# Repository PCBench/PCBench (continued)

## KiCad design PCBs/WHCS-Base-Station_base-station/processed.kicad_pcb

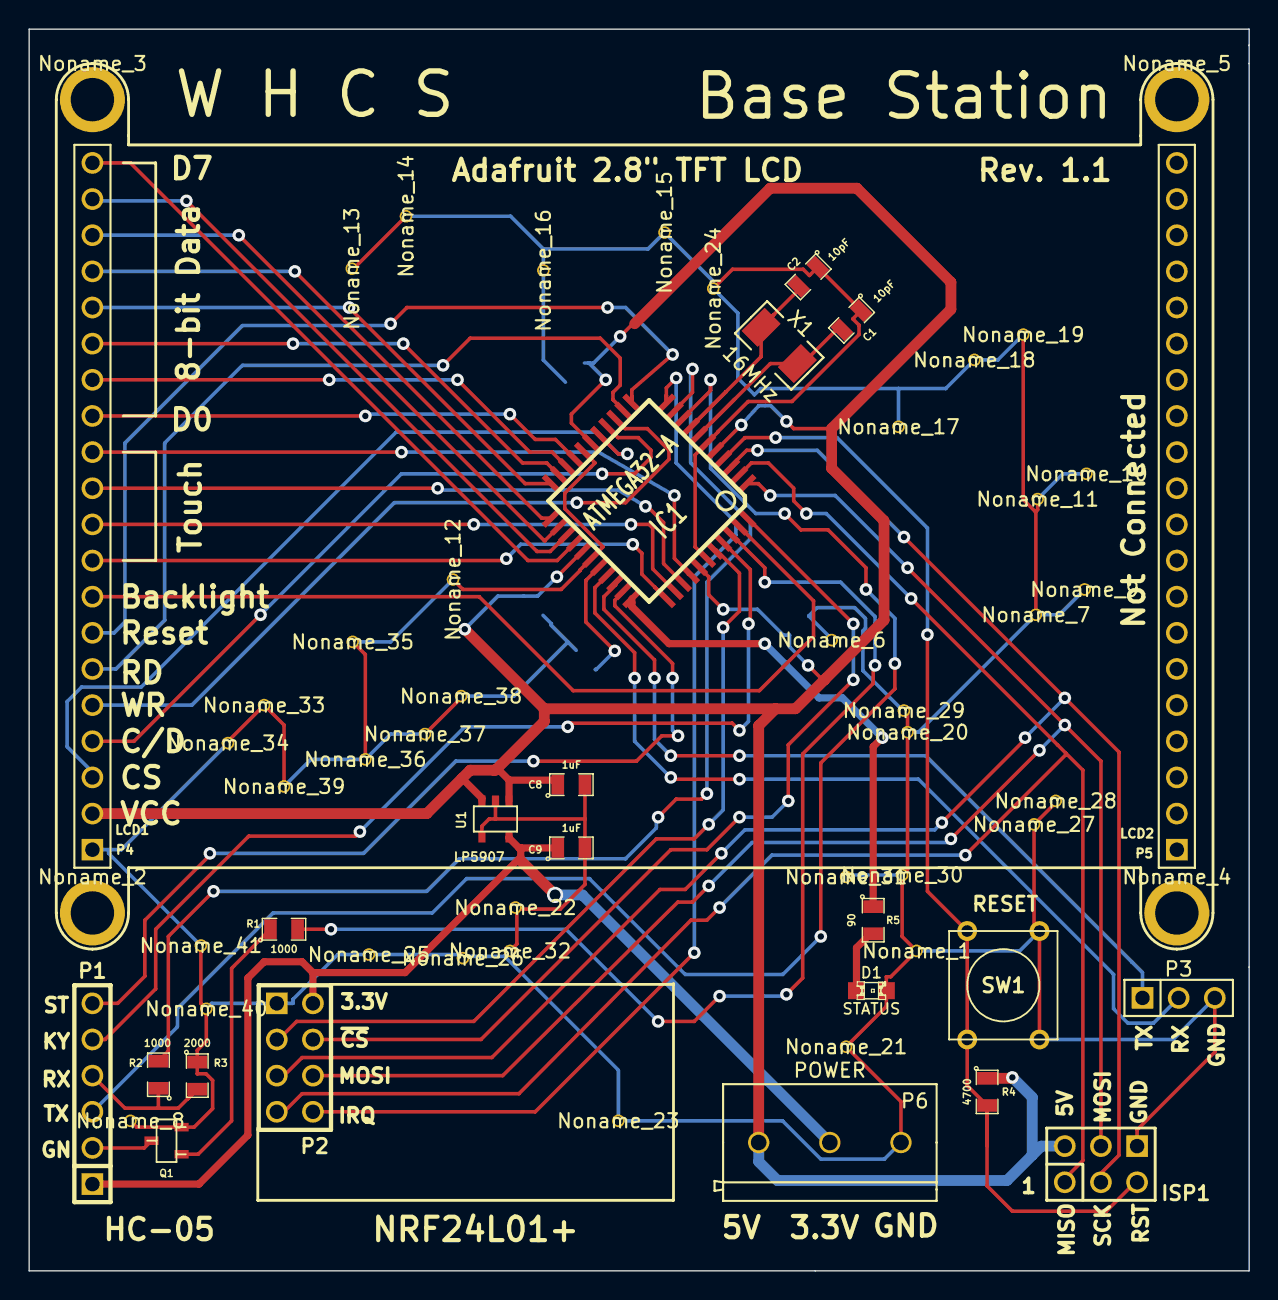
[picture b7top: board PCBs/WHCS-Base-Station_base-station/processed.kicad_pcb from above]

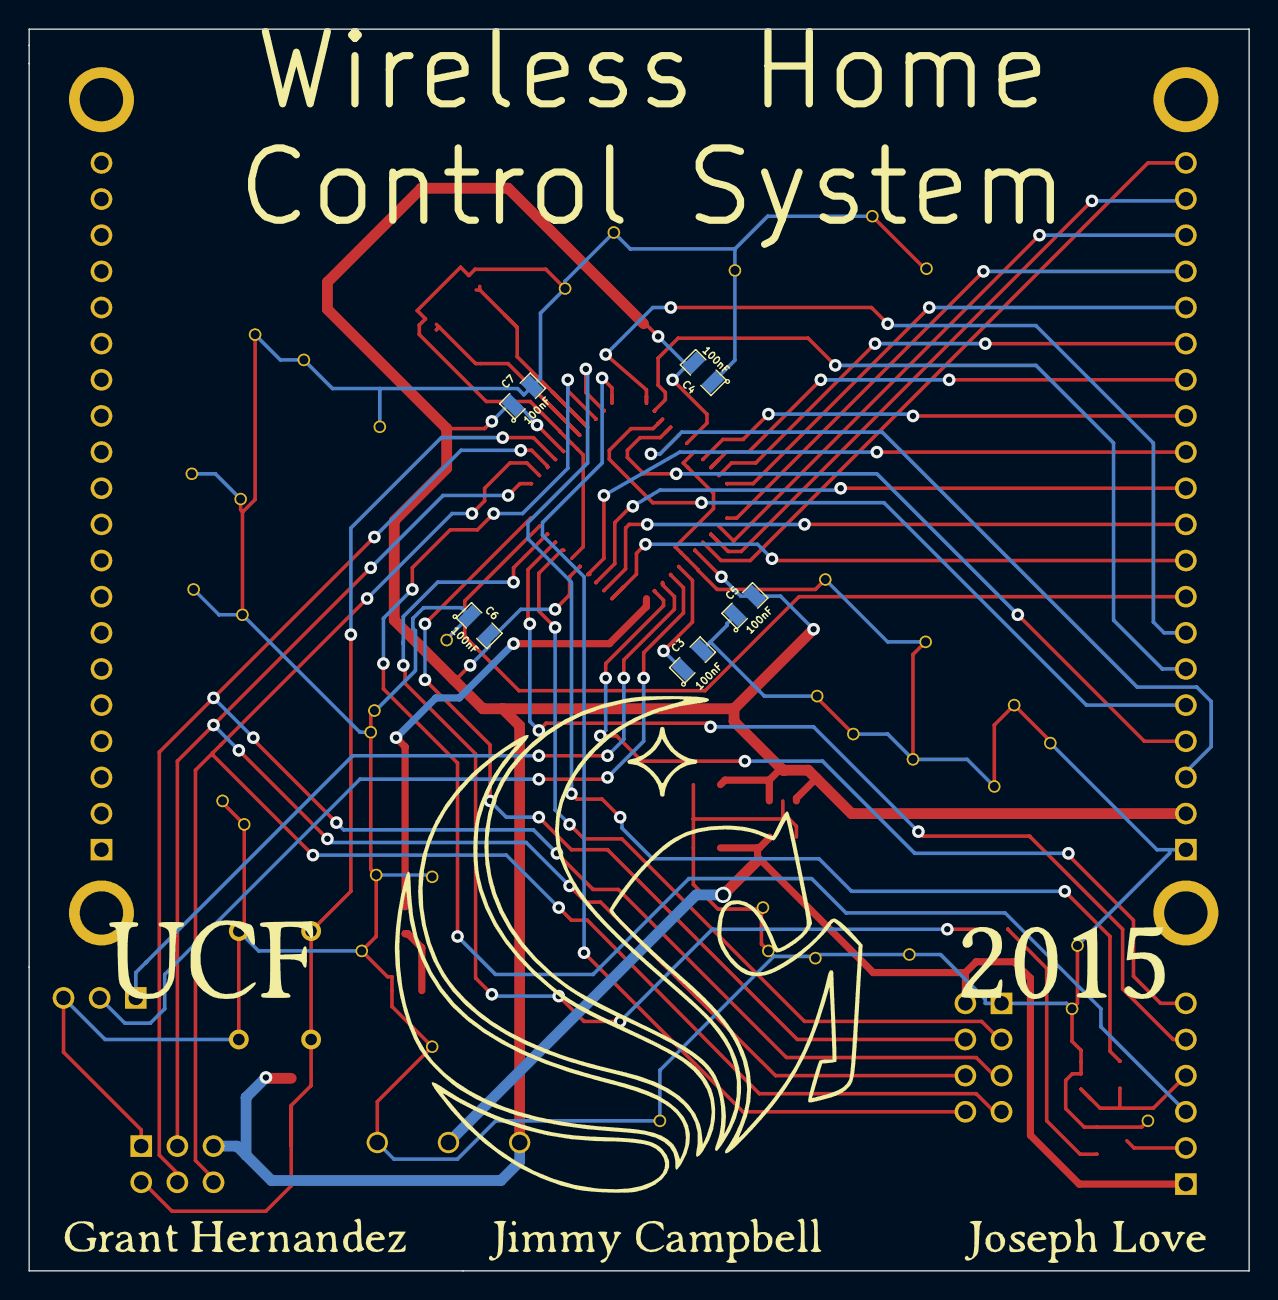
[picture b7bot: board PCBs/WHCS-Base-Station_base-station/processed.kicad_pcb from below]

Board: 2 copper layers, 85.7 x 87.2 mm, 68 parts (5 on the bottom side), 43 nets.

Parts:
C1, C2: 10pF; SM0805
C3, C4, C5, C6, C7: 100nF; SM0805
C8, C9: 1uF; SM0805
D1: STATUS; LED-0805
IC1: ATMEGA32-A; TQFP44
ISP1: ISP; pin_array_3x2
Noname_1, Noname_6, Noname_7, Noname_8, Noname_9, Noname_10, Noname_11, Noname_12, Noname_13, Noname_14, Noname_15, Noname_16, Noname_17, Noname_18, Noname_19, Noname_20, Noname_21, Noname_22, Noname_23, Noname_24, Noname_25, Noname_26, Noname_27, Noname_28, Noname_29, Noname_30, Noname_31, Noname_32, Noname_33, Noname_34, Noname_35, Noname_36, Noname_37, Noname_38, Noname_39, Noname_40, Noname_41: gnd-via
Noname_2, Noname_3, Noname_4, Noname_5: adafruit-tft-mount
P1: HC-05; PIN_ARRAY-6X1
P2: NRF24L01+; pin_array_4x2
P3: SERIAL; PIN_ARRAY_3X1
P4: LCD1; PIN_ARRAY_20X1
P5: LCD2; PIN_ARRAY_20X1
P6: POWER; terminal-282836-3
Q1: BTEN; sot23
R1, R2: 1000; SM0805
R3: 2000; SM0805
R4: 4700; SM0805
R5: 90; SM0805
SW1: RESET; SW_PUSH_SMALL
U1: LP5907; SOT23-5
X1: 16MHz; 2-SMD

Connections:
/3V3: C9.1, P1.1, P2.2, P6.2, U1.5
/BTEN: IC1.42, R1.2
/CD: IC1.15, P4.4
/CE: IC1.40, P2.3
/CSN: IC1.44, P2.4
/D0: IC1.19, P4.13
/D1: IC1.20, P4.14
/D2: IC1.21, P4.15
/D3: IC1.22, P4.16
/D4: IC1.23, P4.17
/D5: IC1.24, P4.18
/D6: IC1.25, P4.19
/D7: IC1.26, P4.20
/HC_GND: P1.2, Q1.2
/IRQ: IC1.11, P2.8
/KEY: IC1.41, P1.5
/LCS: IC1.16, P4.3
/LITE: IC1.43, P4.8
/LRST: IC1.12, P4.7
/MISO: IC1.2, ISP1.1, P2.7
/MOSI: IC1.1, ISP1.4, P2.6
/PA4: IC1.33, R5.1
/RD: IC1.13, P4.6
/RST: IC1.4, ISP1.5, R4.2, SW1.1
/RX: IC1.9, P1.3
/RX_SOFT: IC1.30, P3.2
/SCK: IC1.3, ISP1.3, P2.5
/STATUS: IC1.32, P1.6
/TX: IC1.10, R2.2
/TX_SOFT: IC1.31, P3.1
/VCC: C4.2, C5.2, C6.2, C7.1, C8.1, IC1.5, IC1.17, IC1.27, IC1.38, ISP1.2, P4.2, P6.1, R4.1, U1.1, U1.3
/WR: IC1.14, P4.5
/X+: IC1.34, P4.9
/X-: IC1.36, P4.11
/Y+: IC1.35, P4.10
/Y-: IC1.37, P4.12
GND: C1.1, C2.1, C3.2, C4.1, C5.1, C6.1, C7.2, C8.2, C9.2, D1.2, IC1.6, IC1.18, IC1.28, IC1.39, ISP1.6, P2.1, P3.3, P4.1, P6.3, Q1.3, R3.1, SW1.2, U1.2, U1.4
unnamed: C1.2, IC1.7, X1.2
unnamed: C2.2, IC1.8, X1.1
unnamed: Q1.1, R1.1
unnamed: P1.4, R2.1, R3.2
unnamed: D1.1, R5.2
unnamed: C3.1, IC1.29
